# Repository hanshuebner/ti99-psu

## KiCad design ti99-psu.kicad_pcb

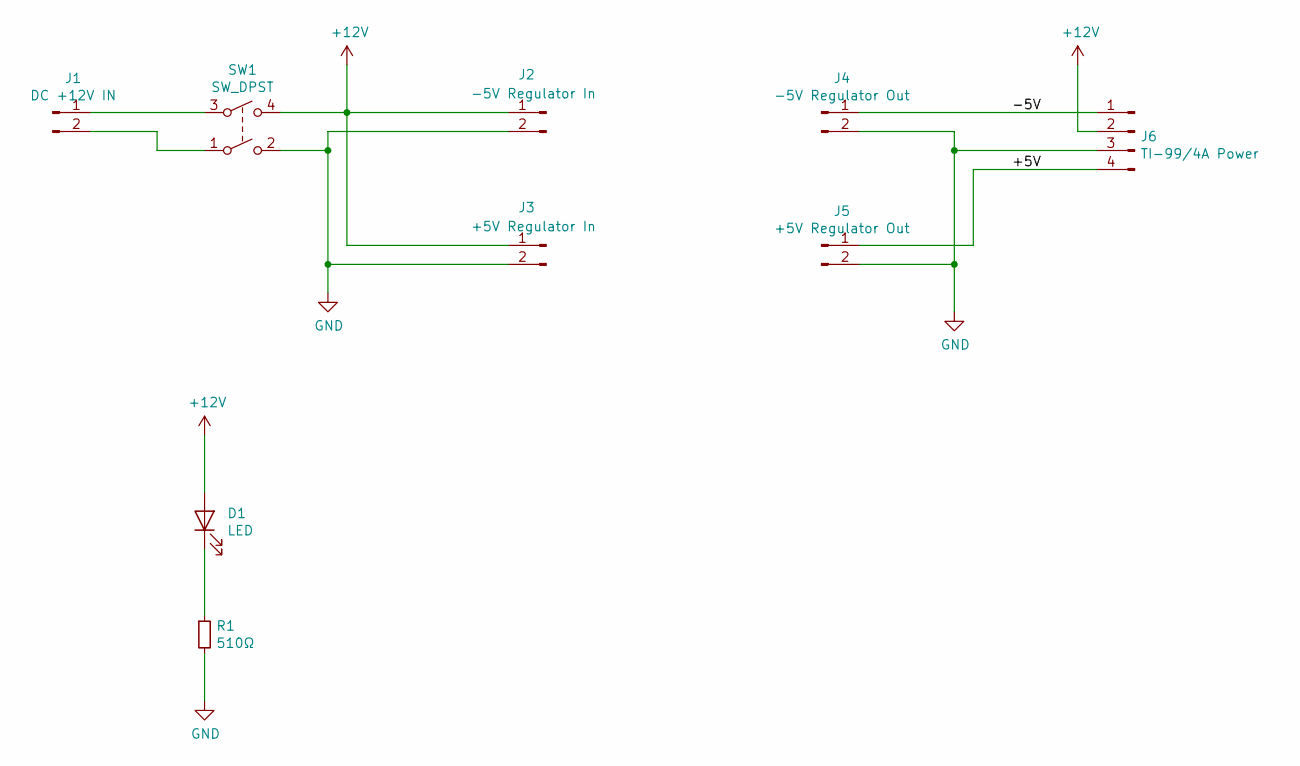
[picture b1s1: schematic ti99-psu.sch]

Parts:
D1: LED; LED_D5.0mm
J1: DC +12V IN; Molex_KK-254_AE-6410-02A_1x02_P2.54mm_Vertical
J2: -5V Regulator In; Molex_KK-254_AE-6410-02A_1x02_P2.54mm_Vertical
J3: +5V Regulator In; Molex_KK-254_AE-6410-02A_1x02_P2.54mm_Vertical
J4: -5V Regulator Out; Molex_KK-254_AE-6410-02A_1x02_P2.54mm_Vertical
J5: +5V Regulator Out; Molex_KK-254_AE-6410-02A_1x02_P2.54mm_Vertical
J6: TI-99/4A Power; Molex_KK-396_A-41791-0004_1x04_P3.96mm_Vertical
R1: 510Ω; R_Axial_DIN0207_L6.3mm_D2.5mm_P7.62mm_Horizontal
SW1: SW_DPST; SW_Slider_DPST

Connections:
+12V: D1.2 (A), J2.1, J3.1, J6.2, SW1.4
/+5V: J5.1, J6.4
/-5V: J4.1, J6.1
GND: J2.2, J3.2, J4.2, J5.2, J6.3, R1.2, SW1.2
unnamed: D1.1 (K), R1.1
unnamed: J1.1, SW1.3
unnamed: J1.2, SW1.1

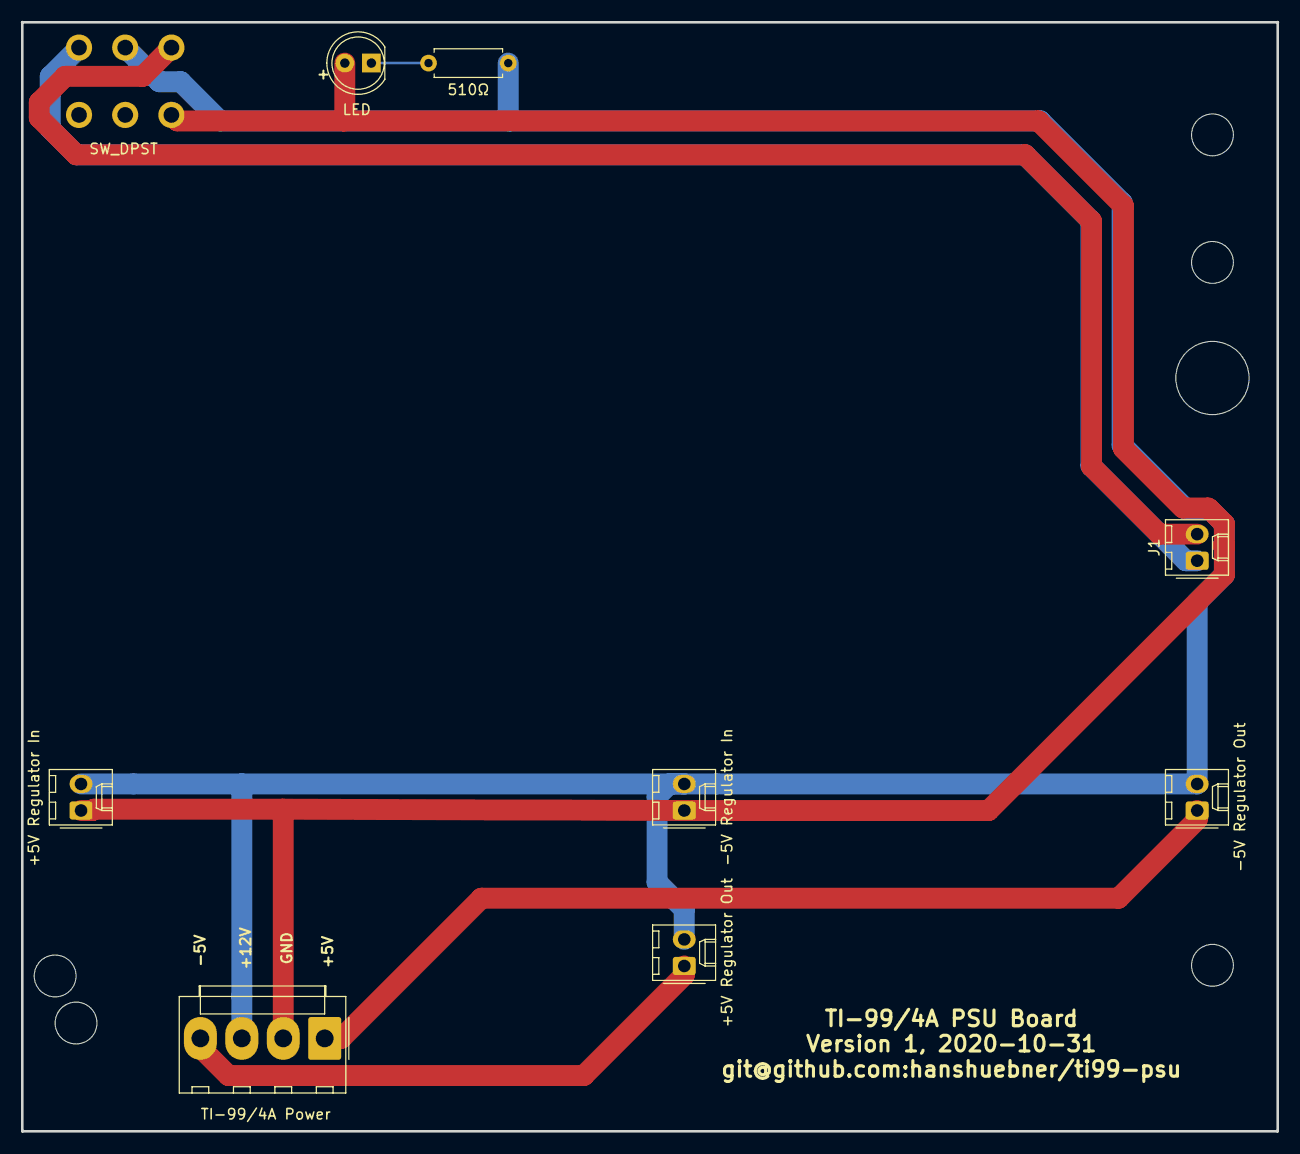
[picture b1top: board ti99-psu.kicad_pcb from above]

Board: 2 copper layers, 120.0 x 106.0 mm, 9 parts (0 on the bottom side), 7 nets.

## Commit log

2020-10-30 Save initial schematics
2020-10-31 V1 sent to production
